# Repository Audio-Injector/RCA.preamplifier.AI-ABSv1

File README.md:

RCA preamplifier

A single ended preamplifier based on the Audio Injector Analogue Breakout Standard v1 (AI-ABS v1)

https://github.com/Audio-Injector/AudioInjector-Analogue-Breakout-Standard

https://www.audioinjector.net/rca-preamp

https://shop.audioinjector.net/detail/Sound_Cards/RCA+preamplifier

Check the balanced (XLR) preamplifier here : https://github.com/Audio-Injector/XLR.preamplifier.AI-ABSv1

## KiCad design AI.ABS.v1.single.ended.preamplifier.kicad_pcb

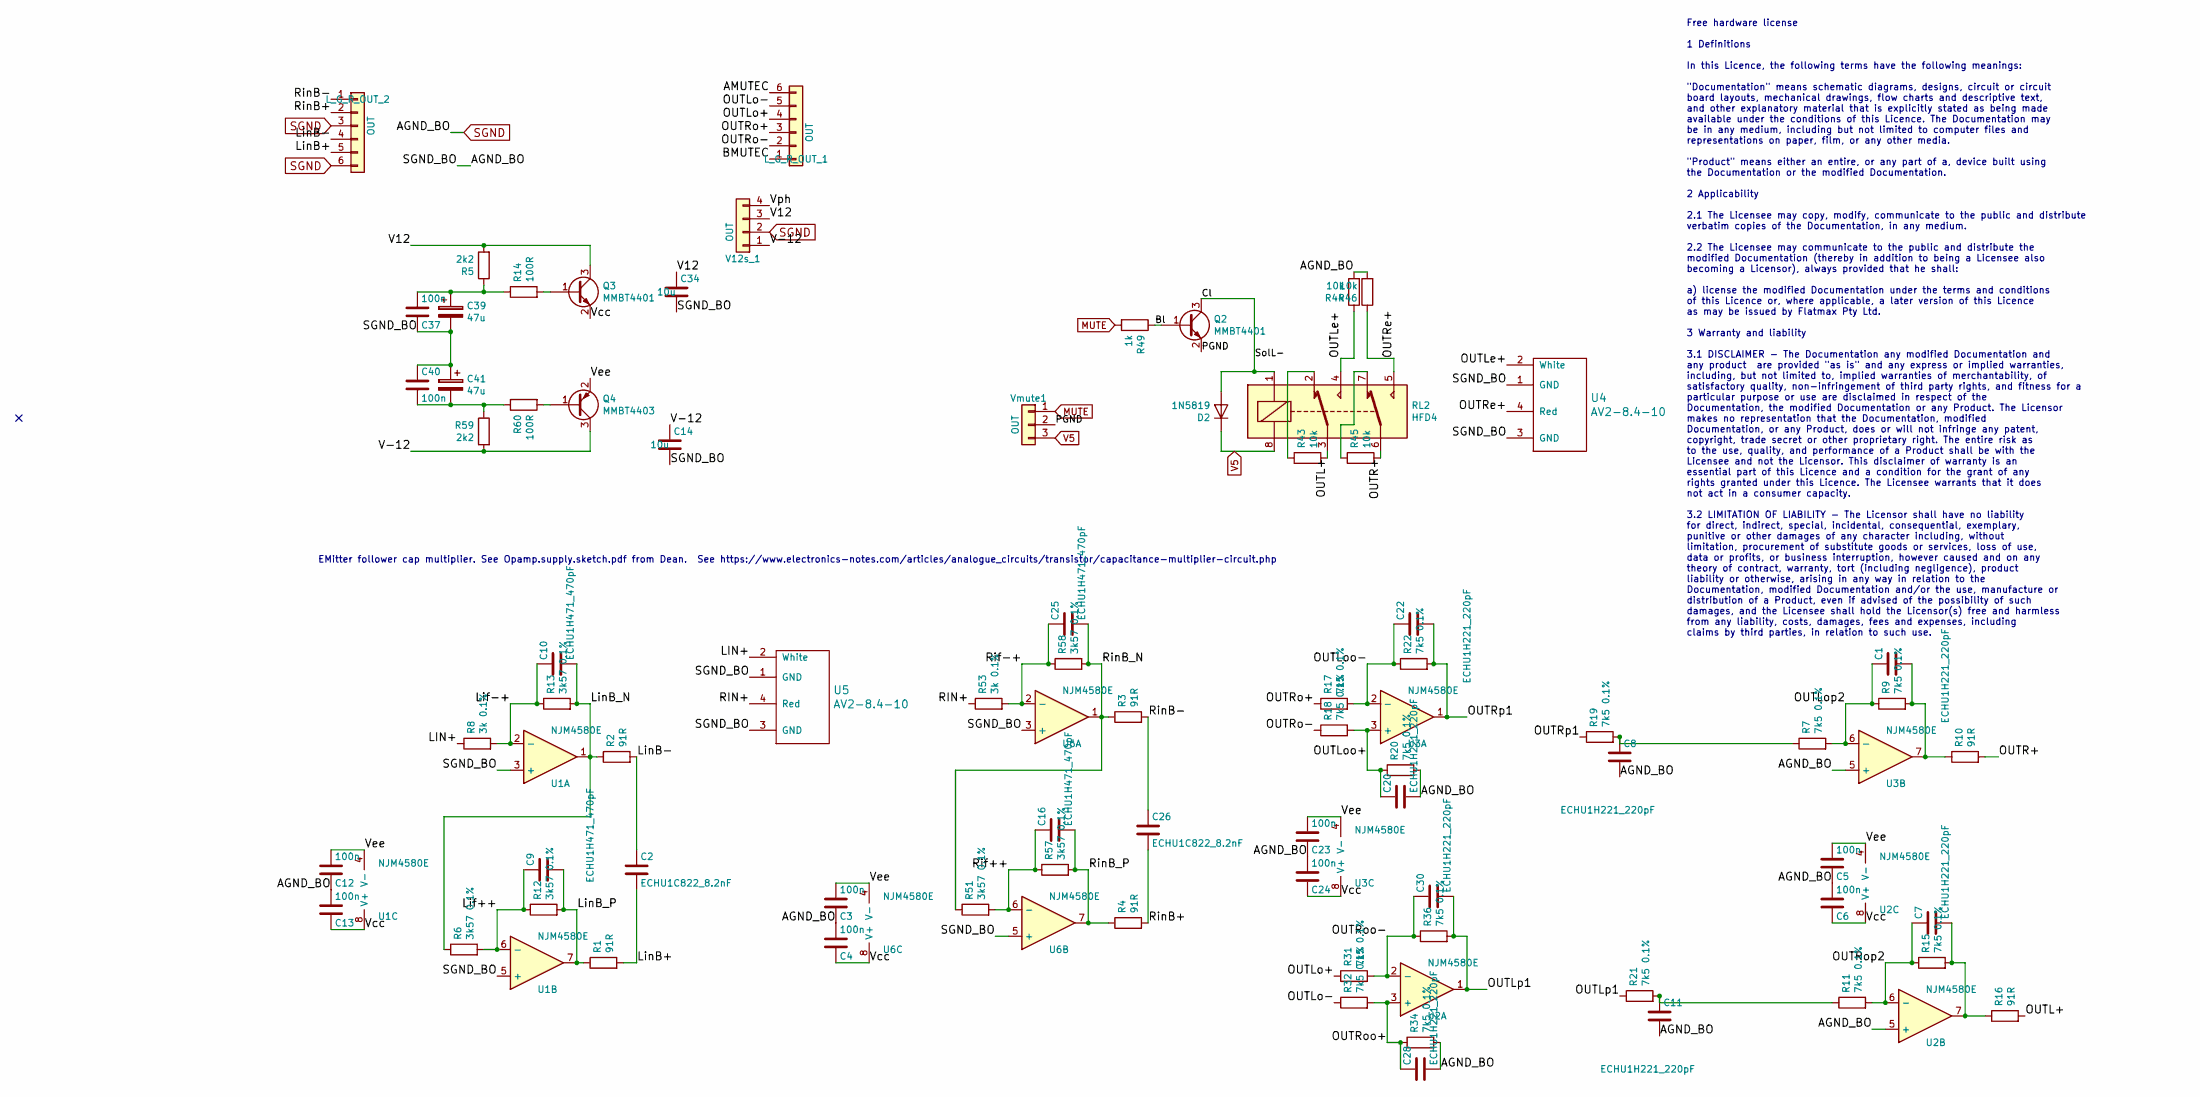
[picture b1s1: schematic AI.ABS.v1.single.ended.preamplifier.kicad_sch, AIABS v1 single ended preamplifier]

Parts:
C1, C7, C8, C11, C20, C22, C28, C30: ECHU1H221_220pF; C_0805_2012Metric
C2, C26: ECHU1C822_8.2nF; C_0805_2012Metric
C3, C4, C5, C6, C12, C13, C23, C24, C37, C40: 100n; C_0603_1608Metric
C9, C10, C16, C25: ECHU1H471_470pF; C_0805_2012Metric
C14, C34: 10u; C_0805_2012Metric
C39, C41: 47u; CP_Elec_6.3x7.7
D2: 1N5819; D_SOD-123
L_G_R_OUT_1, L_G_R_OUT_2: OUT; PinHeader_1x06_P2.54mm_Vertical
Q2, Q3: MMBT4401; SOT-23
Q4: MMBT4403; SOT-23
R1, R2, R3, R4, R10, R16: 91R; R_0603_1608Metric
R5, R59: 2k2; R_0603_1608Metric
R6, R12, R13, R51, R57, R58: 3k57 0.1%; R_0603_1608Metric
R7, R9, R11, R15, R17, R18, R19, R20, R21, R22, R31, R32, R34, R36: 7k5 0.1%; R_0603_1608Metric
R8, R53: 3k 0.1%; R_0603_1608Metric
R14, R60: 100R; R_0603_1608Metric
R43, R44, R45, R46: 10k; R_0603_1608Metric
R49: 1k; R_0603_1608Metric
RL2: HFD4; HDF4
U1, U2, U3, U6: NJM4580E; SOIC-8_3.9x4.9mm_P1.27mm
U4, U5: AV2-8.4-10
V12s_1: OUT; PinHeader_1x04_P2.54mm_Vertical
Vmute1: OUT; PinHeader_1x03_P2.54mm_Vertical

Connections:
/AMUTEC: L_G_R_OUT_1.6
/BMUTEC: L_G_R_OUT_1.1
/Bl: Q2.1 (B), R49.1
/Cl: D2.2 (A), Q2.3 (C), RL2.1
/LIN+: R8.1, U5.2 (White)
/Lif++: C9.1, R6.2, R12.1, U1.6 (-)
/Lif-+: C10.1, R8.2, R13.1, U1.2 (-)
/LinB+: C2.2, L_G_R_OUT_2.5, R1.2
/LinB-: C2.1, L_G_R_OUT_2.4, R2.2
/LinB_N: C10.2, R2.1, R6.1, R13.2, U1.1
/LinB_P: C9.2, R1.1, R12.2, U1.7
/OUTL+: R16.2, R43.2, RL2.3
/OUTLe+: R44.1, RL2.4, U4.2 (White)
/OUTLo+: L_G_R_OUT_1.4, R31.1
/OUTLo-: L_G_R_OUT_1.5, R32.1
/OUTLoo+: C20.1, R18.2, R20.1, U3.3 (+)
/OUTLoo-: C22.1, R17.2, R22.1, U3.2 (-)
/OUTLop2: C1.1, R7.2, R9.1, U3.6 (-)
/OUTLp1: C30.2, R21.1, R36.2, U2.1
/OUTR+: R10.2, R45.2, RL2.6
/OUTRe+: R46.1, RL2.5, U4.4 (Red)
/OUTRo+: L_G_R_OUT_1.3, R17.1
/OUTRo-: L_G_R_OUT_1.2, R18.1
/OUTRoo+: C28.1, R32.2, R34.1, U2.3 (+)
/OUTRoo-: C30.1, R31.2, R36.1, U2.2 (-)
/OUTRop2: C7.1, R11.2, R15.1, U2.6 (-)
/OUTRp1: C22.2, R19.1, R22.2, U3.1
/PGND: Q2.2 (E), Vmute1.2
/RIN+: R53.1, U5.4 (Red)
/Rif++: C16.1, R51.2, R57.1, U6.6 (-)
/Rif-+: C25.1, R53.2, R58.1, U6.2 (-)
/RinB+: C26.2, L_G_R_OUT_2.2, R4.2
/RinB-: C26.1, L_G_R_OUT_2.1, R3.2
/RinB_N: C25.2, R3.1, R51.1, R58.2, U6.1
/RinB_P: C16.2, R4.1, R57.2, U6.7
/V12: C34.1, Q3.3 (C), R5.2, V12s_1.3
/V-12: C14.1, Q4.3 (C), R59.2, V12s_1.1
/Vcc: C4.1, C6.1, C13.1, C24.1, Q3.2 (E), U1.8 (V+), U2.8 (V+), U3.8 (V+), U6.8 (V+)
/Vee: C3.2, C5.2, C12.2, C23.2, Q4.2 (E), U1.4 (V-), U2.4 (V-), U3.4 (V-), U6.4 (V-)
/Vph: V12s_1.4
MUTE: R49.2, Vmute1.1
unnamed: C1.2, R9.2, R10.1, U3.7
unnamed: C7.2, R15.2, R16.1, U2.7
unnamed: C8.1, R7.1, R19.2
unnamed: C11.1, R11.1, R21.2
unnamed: C37.2, C39.1, R5.1, R14.1
unnamed: C40.2, C41.2, R59.1, R60.1
unnamed: Q3.1 (B), R14.2
unnamed: Q4.1 (B), R60.2
unnamed: R43.1, RL2.2
unnamed: R45.1, RL2.7
SGND: C3.1, C4.2, C5.1, C6.2, C8.2, C11.2, C12.1, C13.2, C14.2, C20.2, C23.1, C24.2, C28.2, C34.2, C37.1, C39.2, C40.1, C41.1, L_G_R_OUT_2.3, L_G_R_OUT_2.6, R20.2, R34.2, R44.2, R46.2, U1.3 (+), U1.5 (+), U2.5 (+), U3.5 (+), U4.1 (GND), U4.3 (GND), U5.1 (GND), U5.3 (GND), U6.3 (+), U6.5 (+), V12s_1.2
V5: D2.1 (K), RL2.8, Vmute1.3

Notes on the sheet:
Free hardware license 1 Definitions In this Licence, the following terms have the following meanings: "Documentation" means schematic diagrams, designs, circuit or circuit board layouts, mechanical drawings, flow charts and descriptive text, and other explanatory material that is explicitly stated 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
EMitter follower cap multiplier. See Opamp.supply.sketch.pdf from Dean. See https://www.electronics-notes.com/articles/analogue_circuits/transistor/capacitance-multiplier-circuit.php

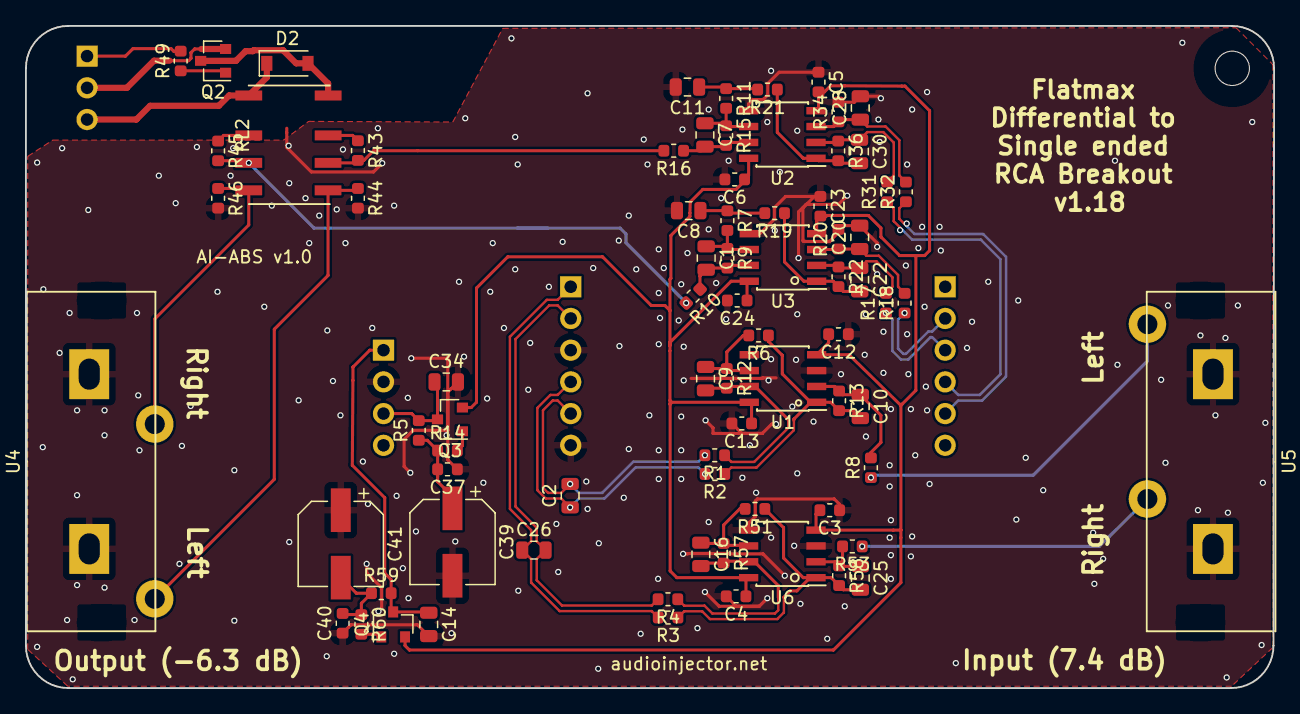
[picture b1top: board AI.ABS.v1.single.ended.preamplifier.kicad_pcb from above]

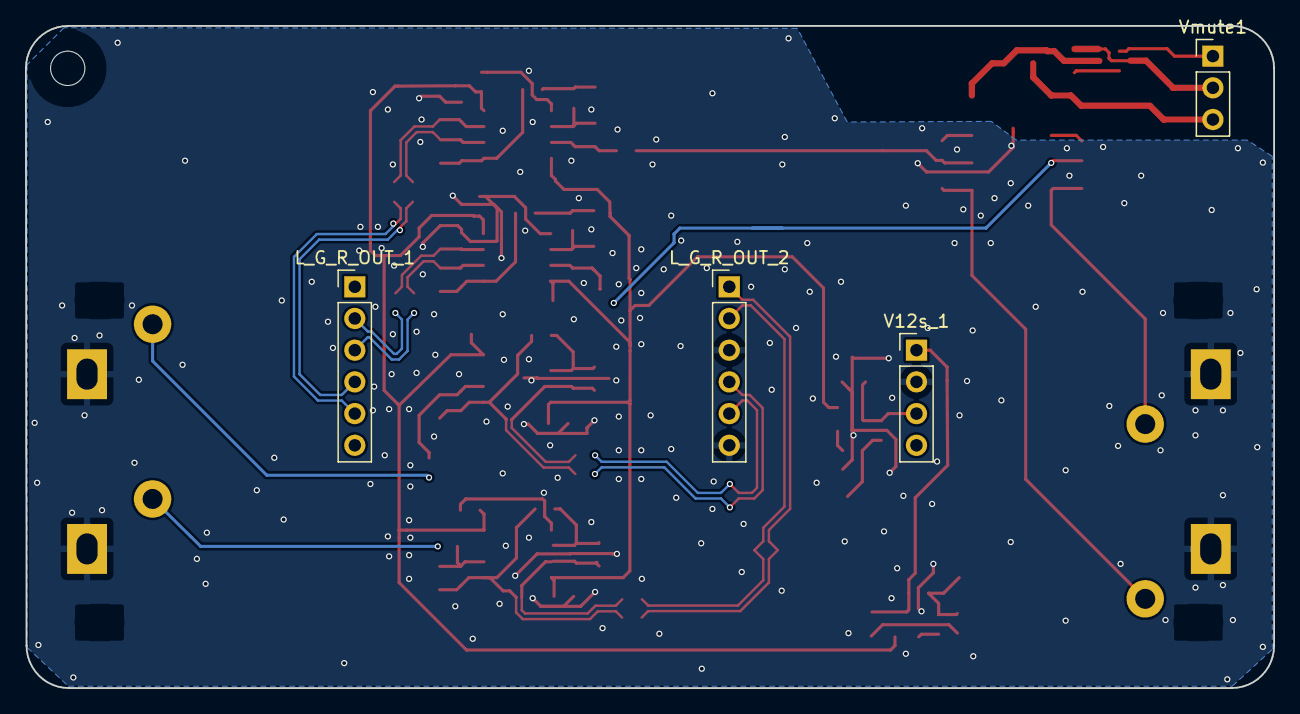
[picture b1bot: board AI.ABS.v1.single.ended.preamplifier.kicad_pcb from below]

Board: 4 copper layers, 100.0 x 53.1 mm, 80 parts (4 on the bottom side), 50 nets.

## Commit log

2022-08-30 v1.18
2022-08-31 Removed un-necessary files and added the title block.
2022-08-31 updated a link to the XLR preamplifier
2022-08-31 removed some un-necessary files

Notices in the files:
AI.ABS.v1.single.ended.preamplifier.kicad_pcb:
available under the conditions of this Licence. The Documentation may
rights granted under this Licence. The Licensee warrants that it does
